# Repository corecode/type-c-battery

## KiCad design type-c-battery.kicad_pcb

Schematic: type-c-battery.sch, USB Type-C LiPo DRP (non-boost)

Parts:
C1, C5: 0.1u; SMD-1005
C2: 120u; SMD-3528-CP; Part Number TCJB157M006R0055
C3, C4: 4.7u; SMD-1608; Part Number CL10B475KQ8NQNC
D1: LED; SMD-1608-LED
J1: BAT; JST-PH-2-RIGHT-SMD; Part Number S2B-PH-SM4-TB(LF)(SN)
J2: USB Type-C Receptacle; USB-TYPE-C-DX07B024JJ1; Part Number DX07B024JJ2R1500
R1, R5: 200k; SMD-1005
R2: 5k; SMD-1005
R3: 2k; SMD-1005
R4: 900k; SMD-1005
U1: AP2161; SOT-23-5; Part Number AP2161WG-7
U2: TP4055; SOT-23-5
U3: TUSB320HA; X2QFN-12; Part Number TUSB320HAIRWBR

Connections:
/CC1: J2.A5 (CC1), U3.1 (CC1)
/CC2: J2.B5 (CC2), U3.2 (CC2)
/~DFP: R1.2, U1.4, U3.9 (ID)
/~ERR: R5.2, U1.3, U3.11 (EN)
COM: C1.2, C2.-, C3.2, C4.2, C5.2, J1.1, J2.A1 (GND), J2.A12 (GND), J2.B1 (GND), J2.B12 (GND), J2.SHEL (SHELL), R3.2, U1.2, U2.2 (GND), U3.10 (GND)
unnamed: D1.A, R2.2
unnamed: D1.C, U2.1 (~CHRG)
unnamed: R3.1, U2.5 (PROG)
unnamed: R4.2, U3.4 (VBUS_DET)
VBAT: C1.1, C2.+, C4.1, C5.1, J1.2, R1.1, R5.1, U1.5, U2.3 (BAT), U3.12 (VDD)
VBUS: C3.1, J2.A4 (VBUS), J2.A9 (VBUS), J2.B4 (VBUS), J2.B9 (VBUS), R2.1, R4.1, U1.1, U2.4 (VCC)

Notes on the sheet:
PORT = float for DRP ADDR = float for GPIO

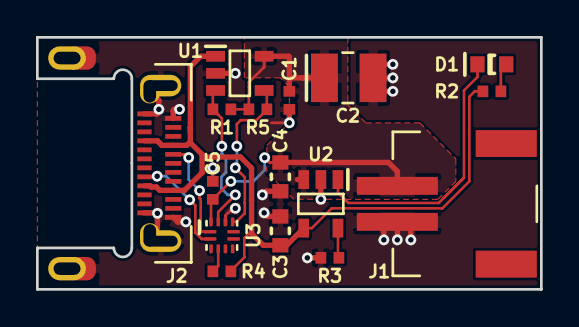
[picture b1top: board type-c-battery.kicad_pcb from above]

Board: 2 copper layers, 28.0 x 14.0 mm, 16 parts (0 on the bottom side), 11 nets.

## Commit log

2017-07-02 type-c DRP, non-boost
2017-07-03 boost design
2017-07-07 add wire
2017-07-14 layout
2017-07-14 update libs
2017-07-14 update cap values
